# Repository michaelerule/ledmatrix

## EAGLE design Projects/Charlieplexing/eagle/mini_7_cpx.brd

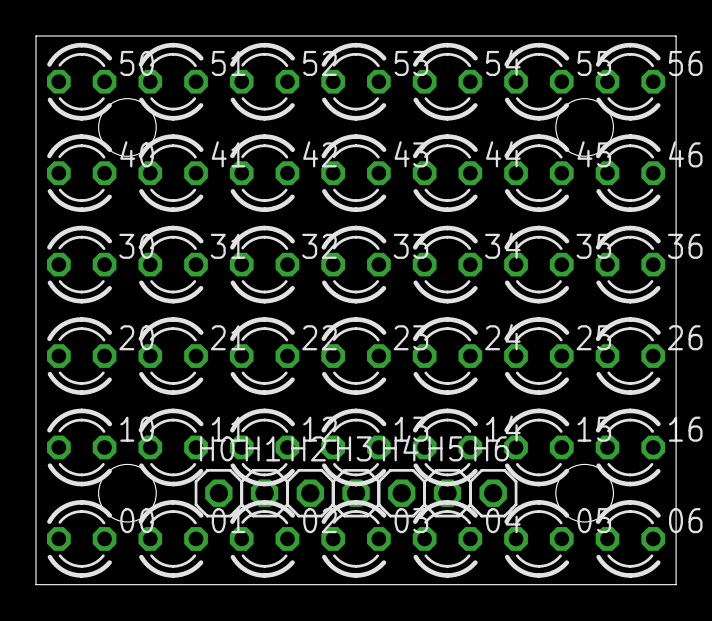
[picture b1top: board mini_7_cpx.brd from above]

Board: 2 copper layers, 35.6 x 30.5 mm, 49 parts (0 on the bottom side), 7 nets, no tracks yet.

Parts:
00, 01, 02, 03, 04, 05, 06, 10, 11, 12, 13, 14, 15, 16, 20, 21, 22, 23, 24, 25, 26, 30, 31, 32, 33, 34, 35, 36, 40, 41, 42, 43, 44, 45, 46, 50, 51, 52, 53, 54, 55, 56: LED3MM
H0, H1, H2, H3, H4, H5, H6: 1X01

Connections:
D: 00.A, 06.K, 11.A, 16.K, 22.A, 26.K, 33.A, 36.K, 44.A, 46.K, 55.A, 56.K, H6.1
S0: 00.K, 01.A, 02.A, 03.A, 04.A, 05.A, 06.A, 10.K, 20.K, 30.K, 40.K, 50.K, H0.1
S1: 01.K, 10.A, 11.K, 12.A, 13.A, 14.A, 15.A, 16.A, 21.K, 31.K, 41.K, 51.K, H1.1
S2: 02.K, 12.K, 20.A, 21.A, 22.K, 23.A, 24.A, 25.A, 26.A, 32.K, 42.K, 52.K, H2.1
S3: 03.K, 13.K, 23.K, 30.A, 31.A, 32.A, 33.K, 34.A, 35.A, 36.A, 43.K, 53.K, H3.1
S4: 04.K, 14.K, 24.K, 34.K, 40.A, 41.A, 42.A, 43.A, 44.K, 45.A, 46.A, 54.K, H4.1
S5: 05.K, 15.K, 25.K, 35.K, 45.K, 50.A, 51.A, 52.A, 53.A, 54.A, 55.K, 56.A, H5.1

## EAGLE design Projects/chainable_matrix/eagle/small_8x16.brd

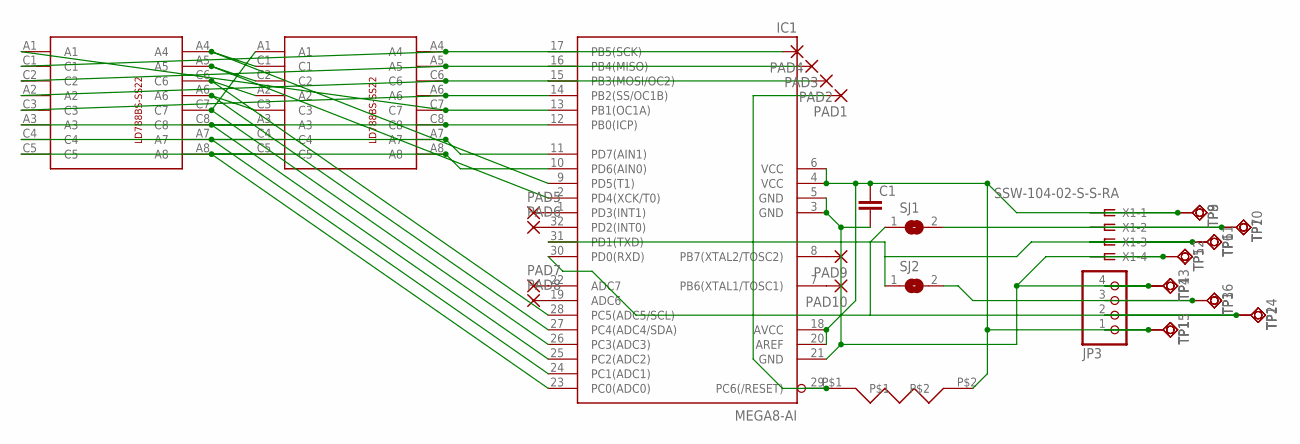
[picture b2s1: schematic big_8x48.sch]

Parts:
C1: CAPPTH; CAP-PTH-SMALL
IC1: MEGA8-AI; TQFP32-08
JP3: PINHD-1X4/90; 1X04/90
PAD1, PAD2, PAD3, PAD4, PAD5, PAD6, PAD7, PAD8, PAD9, PAD10: 1,6/0,8
SJ1, SJ2: SJ
TP1, TP2, TP3, TP4, TP5, TP6, TP7, TP8, TP9, TP10, TP11, TP12, TP13, TP14, TP15, TP16: TPSQTP20SQ; TP20SQ
U$1, U$2: LD-1088BS
U$3: R-6
X1: SSW-104-02-S-S-RA

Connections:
unnamed: IC1.24 (PC1(ADC1)), U$1.A7, U$2.C4
unnamed: IC1.25 (PC2(ADC2)), U$1.C8, U$2.A3
unnamed: IC1.26 (PC3(ADC3)), U$1.C7, U$2.A1
unnamed: IC1.27 (PC4(ADC4/SDA)), U$1.A6, U$2.C3
unnamed: IC1.28 (PC5(ADC5/SCL)), U$1.C6, U$2.A2
unnamed: IC1.2 (PD4(XCK/T0)), U$1.A5, U$2.C2
unnamed: IC1.9 (PD5(T1)), U$1.A4, U$2.C1
unnamed: IC1.15 (PB3(MOSI/OC2)), PAD2.1, U$1.A2, U$2.C6
unnamed: IC1.14 (PB2(SS/OC1B)), U$1.C3, U$2.A6
unnamed: IC1.13 (PB1(OC1A)), U$1.A1, U$2.C7
unnamed: IC1.12 (PB0(ICP)), U$1.A3, U$2.C8
unnamed: IC1.11 (PD7(AIN1)), U$1.C4, U$2.A7
unnamed: IC1.10 (PD6(AIN0)), U$1.C5, U$2.A8
unnamed: IC1.16 (PB4(MISO)), PAD3.1, U$1.C2, U$2.A5
unnamed: IC1.17 (PB5(SCK)), PAD4.1, U$1.C1, U$2.A4
unnamed: IC1.1 (PD3(INT1)), PAD5.1
unnamed: IC1.23 (PC0(ADC0)), U$1.A8, U$2.C5
unnamed: C1.2, IC1.3 (GND), IC1.5 (GND), IC1.21 (GND), JP3.4, TP4.TP, TP5.TP, TP12.TP, TP13.TP, X1.4
unnamed: C1.1, IC1.4 (VCC), IC1.6 (VCC), IC1.18 (AVCC), IC1.20 (AREF), JP3.1, TP1.TP, TP8.TP, TP9.TP, TP15.TP, U$3.P$2, X1.1
unnamed: IC1.32 (PD2(INT0)), PAD6.1
unnamed: SJ1.2, TP7.TP, TP10.TP, X1.2
unnamed: JP3.3, SJ2.2, TP3.TP, TP16.TP
unnamed: IC1.31 (PD1(TXD)), SJ2.1, TP6.TP, TP11.TP, X1.3
unnamed: IC1.30 (PD0(RXD)), JP3.2, SJ1.1, TP2.TP, TP14.TP
unnamed: IC1.29 (PC6(/RESET)), PAD1.1, U$3.P$1
unnamed: IC1.22 (ADC7), PAD7.1
unnamed: IC1.19 (ADC6), PAD8.1
unnamed: IC1.8 (PB7(XTAL2/TOSC2)), PAD9.1
unnamed: IC1.7 (PB6(XTAL1/TOSC1)), PAD10.1

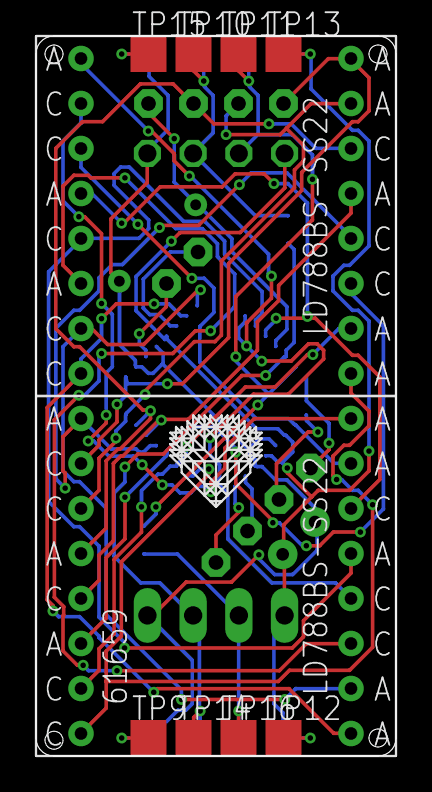
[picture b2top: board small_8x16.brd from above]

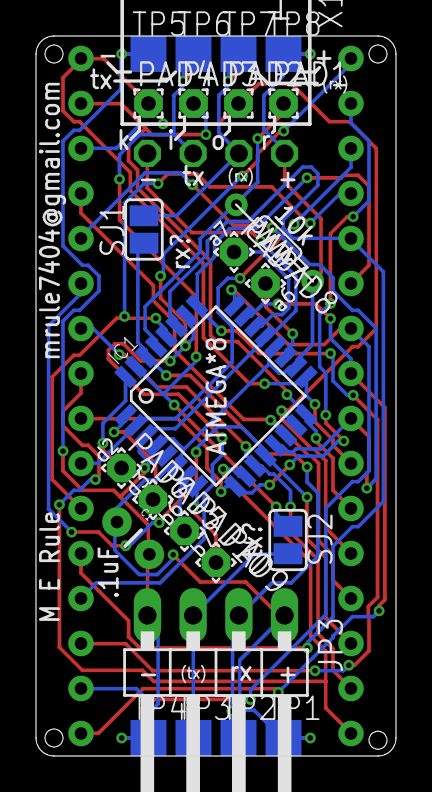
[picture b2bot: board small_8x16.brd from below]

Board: 2 copper layers, 20.0 x 40.0 mm, 36 parts (25 on the bottom side), 29 nets.

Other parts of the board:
U$4: LOGO

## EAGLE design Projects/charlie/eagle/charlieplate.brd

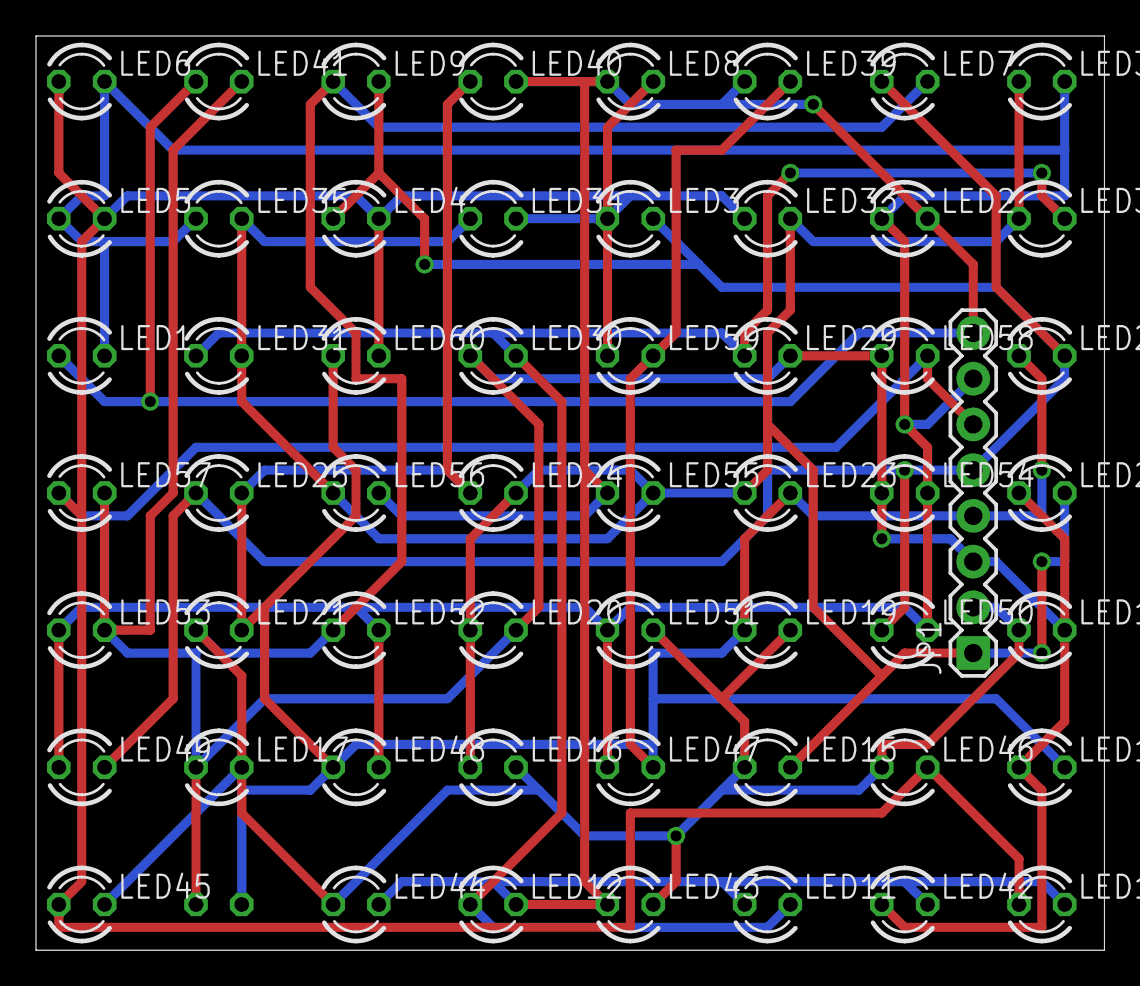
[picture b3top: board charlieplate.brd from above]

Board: 2 copper layers, 59.4 x 50.8 mm, 57 parts (1 on the bottom side), 9 nets.

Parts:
JP1: 1X08
LED1, LED2, LED3, LED4, LED5, LED6, LED7, LED8, LED9, LED10, LED11, LED12, LED13, LED14, LED15, LED16, LED17, LED18, LED19, LED20, LED21, LED22, LED23, LED24, LED25, LED26, LED29, LED30, LED31, LED32, LED33, LED34, LED35, LED36, LED39, LED40, LED41, LED42, LED43, LED44, LED45, LED46, LED47, LED48, LED49, LED50, LED51, LED52, LED53, LED54, LED55, LED56, LED57, LED58, LED59, LED60: LED3MM

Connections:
unnamed: JP1.8, LED1.A, LED2.K, LED8.A, LED10.K, LED11.A, LED12.K, LED39.A, LED40.K, LED41.A, LED42.K, LED43.A, LED44.K, LED55.A, LED56.K
unnamed: LED11.K, LED12.A, LED29.A, LED30.K, LED31.A, LED32.K
unnamed: JP1.1, LED15.K, LED16.A, LED20.A, LED22.K, LED23.A, LED24.K, LED31.K, LED32.A, LED33.K, LED34.A, LED35.K, LED36.A, LED55.K, LED56.A
unnamed: JP1.3, LED13.K, LED14.A, LED17.A, LED18.K, LED20.K, LED22.A, LED29.K, LED30.A, LED41.K, LED42.A, LED53.K, LED54.A, LED57.K, LED58.A
unnamed: JP1.6, LED3.A, LED4.K, LED5.K, LED6.A, LED8.K, LED10.A, LED33.A, LED34.K, LED45.A, LED46.K, LED57.A, LED58.K, LED59.A, LED60.K
unnamed: JP1.4, LED13.A, LED14.K, LED19.A, LED21.K, LED23.K, LED24.A, LED25.K, LED26.A, LED39.K, LED40.A, LED47.K, LED48.A, LED59.K, LED60.A
unnamed: JP1.5, LED3.K, LED4.A, LED7.A, LED9.K, LED25.A, LED26.K, LED49.K, LED50.A
unnamed: JP1.7, LED1.K, LED2.A, LED5.A, LED6.K, LED35.A, LED36.K, LED47.A, LED48.K, LED49.A, LED50.K, LED51.A, LED52.K, LED53.A, LED54.K
unnamed: JP1.2, LED7.K, LED9.A, LED15.A, LED16.K, LED17.K, LED18.A, LED19.K, LED21.A, LED43.K, LED44.A, LED45.K, LED46.A, LED51.K, LED52.A

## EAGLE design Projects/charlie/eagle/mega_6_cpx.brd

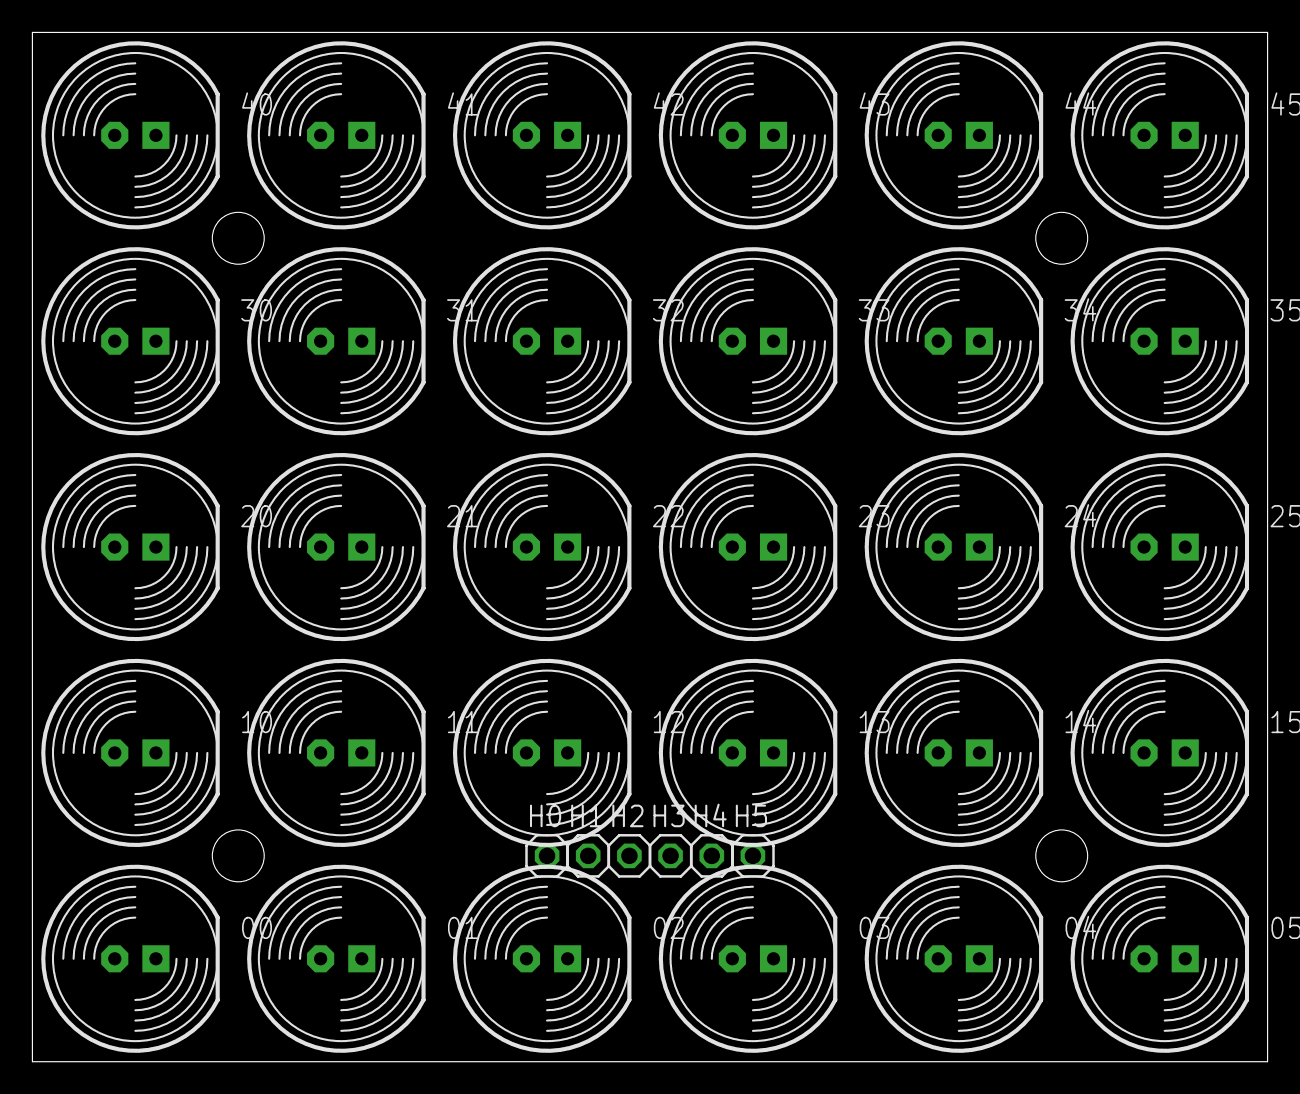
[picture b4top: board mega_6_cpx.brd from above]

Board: 2 copper layers, 76.2 x 63.5 mm, 36 parts (0 on the bottom side), 6 nets, no tracks yet.

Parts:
00, 01, 02, 03, 04, 05, 10, 11, 12, 13, 14, 15, 20, 21, 22, 23, 24, 25, 30, 31, 32, 33, 34, 35, 40, 41, 42, 43, 44, 45: LED10MM
H0, H1, H2, H3, H4, H5: 1X01

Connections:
D: 00.A, 05.K, 11.A, 15.K, 22.A, 25.K, 33.A, 35.K, 44.A, 45.K, H5.1
S0: 00.K, 01.A, 02.A, 03.A, 04.A, 05.A, 10.K, 20.K, 30.K, 40.K, H0.1
S1: 01.K, 10.A, 11.K, 12.A, 13.A, 14.A, 15.A, 21.K, 31.K, 41.K, H1.1
S2: 02.K, 12.K, 20.A, 21.A, 22.K, 23.A, 24.A, 25.A, 32.K, 42.K, H2.1
S3: 03.K, 13.K, 23.K, 30.A, 31.A, 32.A, 33.K, 34.A, 35.A, 43.K, H3.1
S4: 04.K, 14.K, 24.K, 34.K, 40.A, 41.A, 42.A, 43.A, 44.K, 45.A, H4.1

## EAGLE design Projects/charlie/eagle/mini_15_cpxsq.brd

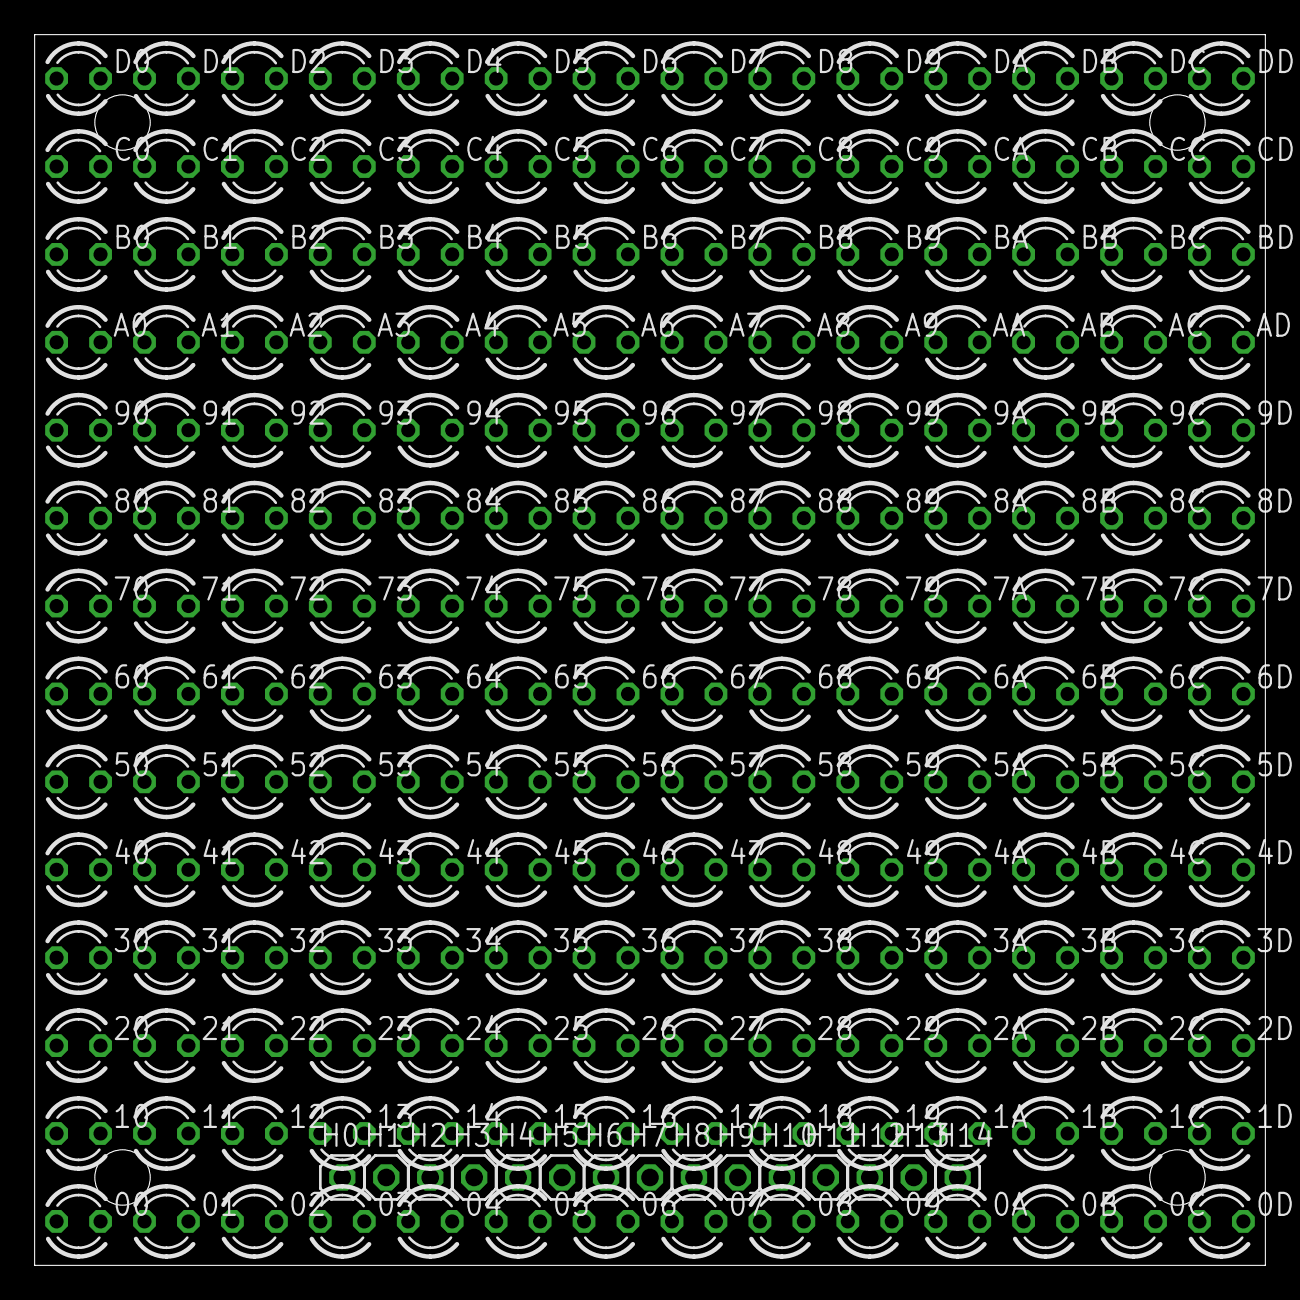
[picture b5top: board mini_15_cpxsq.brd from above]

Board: 2 copper layers, 71.1 x 71.1 mm, 211 parts (0 on the bottom side), 15 nets, no tracks yet.

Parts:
00, 0A, 0B, 0C, 0D, 01, 1A, 1B, 1C, 1D, 02, 2A, 2B, 2C, 2D, 03, 3A, 3B, 3C, 3D, 04, 4A, 4B, 4C, 4D, 05, 5A, 5B, 5C, 5D, 06, 6A, 6B, 6C, 6D, 07, 7A, 7B, 7C, 7D, 08, 8A, 8B, 8C, 8D, 09, 9A, 9B, 9C, 9D, 10, 11, 12, 13, 14, 15, 16, 17, 18, 19, 20, 21, 22, 23, 24, 25, 26, 27, 28, 29, 30, 31, 32, 33, 34, 35, 36, 37, 38, 39, 40, 41, 42, 43, 44, 45, 46, 47, 48, 49, 50, 51, 52, 53, 54, 55, 56, 57, 58, 59, 60, 61, 62, 63, 64, 65, 66, 67, 68, 69, 70, 71, 72, 73, 74, 75, 76, 77, 78, 79, 80, 81, 82, 83, 84, 85, 86, 87, 88, 89, 90, 91, 92, 93, 94, 95, 96, 97, 98, 99: LED3MM
A0, A1, A2, A3, A4, A5, A6, A7, A8, A9: LED3MM
AA: LED3MM
AB: LED3MM
AC: LED3MM
AD: LED3MM
B0, B1, B2, B3, B4, B5, B6, B7, B8, B9: LED3MM
BA: LED3MM
BB: LED3MM
BC: LED3MM
BD: LED3MM
C0, C1, C2, C3, C4, C5, C6, C7, C8, C9: LED3MM
CA: LED3MM
CB: LED3MM
CC: LED3MM
CD: LED3MM
D0, D1, D2, D3, D4, D5, D6, D7, D8, D9: LED3MM
DA: LED3MM
DB: LED3MM
DC: LED3MM
DD: LED3MM
H0, H1, H2, H3, H4, H5, H6, H7, H8, H9, H10, H11, H12, H13, H14: 1X01

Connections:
D: 00.A, 11.A, 22.A, 33.A, 44.A, 55.A, 66.A, 77.A, 88.A, 99.A, AA.A, BB.A, CC.A, DD.A, H14.1
S0: 00.K, 0A.A, 0B.A, 0C.A, 0D.A, 01.A, 02.A, 03.A, 04.A, 05.A, 06.A, 07.A, 08.A, 09.A, 10.K, 20.K, 30.K, 40.K, 50.K, 60.K, 70.K, 80.K, 90.K, A0.K, B0.K, C0.K, D0.K, H0.1
S1: 01.K, 1A.A, 1B.A, 1C.A, 1D.A, 10.A, 11.K, 12.A, 13.A, 14.A, 15.A, 16.A, 17.A, 18.A, 19.A, 21.K, 31.K, 41.K, 51.K, 61.K, 71.K, 81.K, 91.K, A1.K, B1.K, C1.K, D1.K, H1.1
S2: 02.K, 2A.A, 2B.A, 2C.A, 2D.A, 12.K, 20.A, 21.A, 22.K, 23.A, 24.A, 25.A, 26.A, 27.A, 28.A, 29.A, 32.K, 42.K, 52.K, 62.K, 72.K, 82.K, 92.K, A2.K, B2.K, C2.K, D2.K, H2.1
S3: 03.K, 3A.A, 3B.A, 3C.A, 3D.A, 13.K, 23.K, 30.A, 31.A, 32.A, 33.K, 34.A, 35.A, 36.A, 37.A, 38.A, 39.A, 43.K, 53.K, 63.K, 73.K, 83.K, 93.K, A3.K, B3.K, C3.K, D3.K, H3.1
S4: 04.K, 4A.A, 4B.A, 4C.A, 4D.A, 14.K, 24.K, 34.K, 40.A, 41.A, 42.A, 43.A, 44.K, 45.A, 46.A, 47.A, 48.A, 49.A, 54.K, 64.K, 74.K, 84.K, 94.K, A4.K, B4.K, C4.K, D4.K, H4.1
S5: 05.K, 5A.A, 5B.A, 5C.A, 5D.A, 15.K, 25.K, 35.K, 45.K, 50.A, 51.A, 52.A, 53.A, 54.A, 55.K, 56.A, 57.A, 58.A, 59.A, 65.K, 75.K, 85.K, 95.K, A5.K, B5.K, C5.K, D5.K, H5.1
S6: 06.K, 6A.A, 6B.A, 6C.A, 6D.A, 16.K, 26.K, 36.K, 46.K, 56.K, 60.A, 61.A, 62.A, 63.A, 64.A, 65.A, 66.K, 67.A, 68.A, 69.A, 76.K, 86.K, 96.K, A6.K, B6.K, C6.K, D6.K, H6.1
S7: 07.K, 7A.A, 7B.A, 7C.A, 7D.A, 17.K, 27.K, 37.K, 47.K, 57.K, 67.K, 70.A, 71.A, 72.A, 73.A, 74.A, 75.A, 76.A, 77.K, 78.A, 79.A, 87.K, 97.K, A7.K, B7.K, C7.K, D7.K, H7.1
S8: 08.K, 8A.A, 8B.A, 8C.A, 8D.A, 18.K, 28.K, 38.K, 48.K, 58.K, 68.K, 78.K, 80.A, 81.A, 82.A, 83.A, 84.A, 85.A, 86.A, 87.A, 88.K, 89.A, 98.K, A8.K, B8.K, C8.K, D8.K, H8.1
S9: 09.K, 9A.A, 9B.A, 9C.A, 9D.A, 19.K, 29.K, 39.K, 49.K, 59.K, 69.K, 79.K, 89.K, 90.A, 91.A, 92.A, 93.A, 94.A, 95.A, 96.A, 97.A, 98.A, 99.K, A9.K, B9.K, C9.K, D9.K, H9.1
S10: 0A.K, 1A.K, 2A.K, 3A.K, 4A.K, 5A.K, 6A.K, 7A.K, 8A.K, 9A.K, A0.A, A1.A, A2.A, A3.A, A4.A, A5.A, A6.A, A7.A, A8.A, A9.A, AA.K, AB.A, AC.A, AD.A, BA.K, CA.K, DA.K, H10.1
S11: 0B.K, 1B.K, 2B.K, 3B.K, 4B.K, 5B.K, 6B.K, 7B.K, 8B.K, 9B.K, AB.K, B0.A, B1.A, B2.A, B3.A, B4.A, B5.A, B6.A, B7.A, B8.A, B9.A, BA.A, BB.K, BC.A, BD.A, CB.K, DB.K, H11.1
S12: 0C.K, 1C.K, 2C.K, 3C.K, 4C.K, 5C.K, 6C.K, 7C.K, 8C.K, 9C.K, AC.K, BC.K, C0.A, C1.A, C2.A, C3.A, C4.A, C5.A, C6.A, C7.A, C8.A, C9.A, CA.A, CB.A, CC.K, CD.A, DC.K, H12.1
S13: 0D.K, 1D.K, 2D.K, 3D.K, 4D.K, 5D.K, 6D.K, 7D.K, 8D.K, 9D.K, AD.K, BD.K, CD.K, D0.A, D1.A, D2.A, D3.A, D4.A, D5.A, D6.A, D7.A, D8.A, D9.A, DA.A, DB.A, DC.A, DD.K, H13.1

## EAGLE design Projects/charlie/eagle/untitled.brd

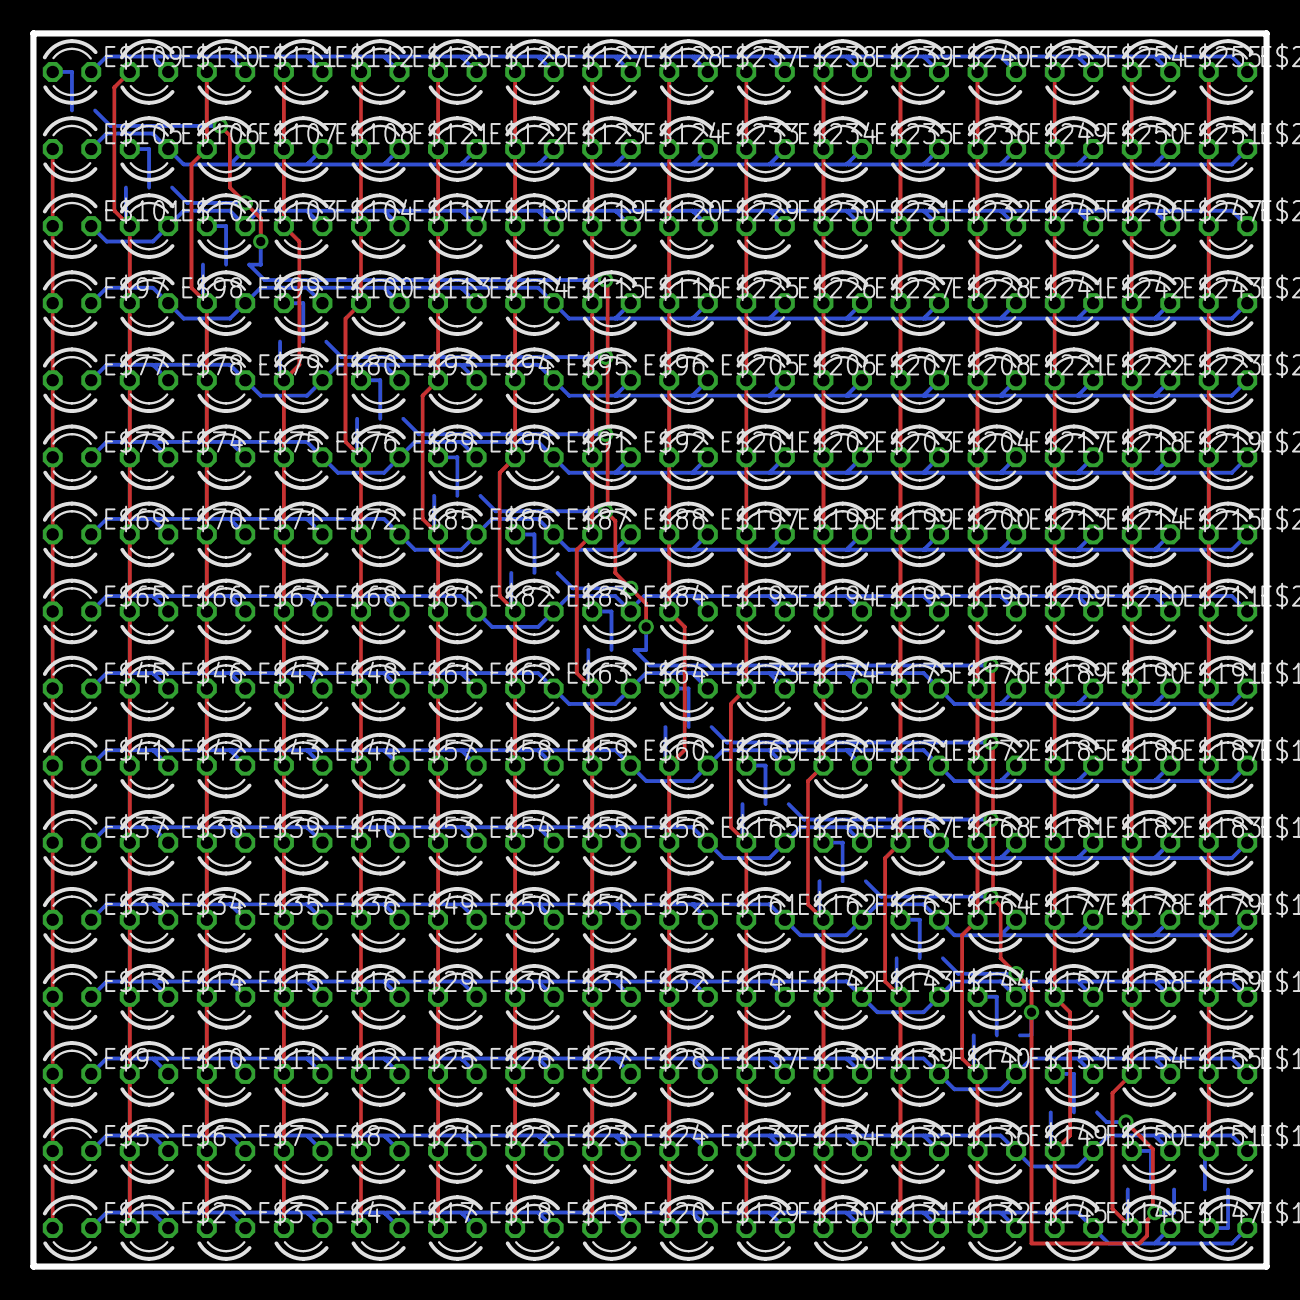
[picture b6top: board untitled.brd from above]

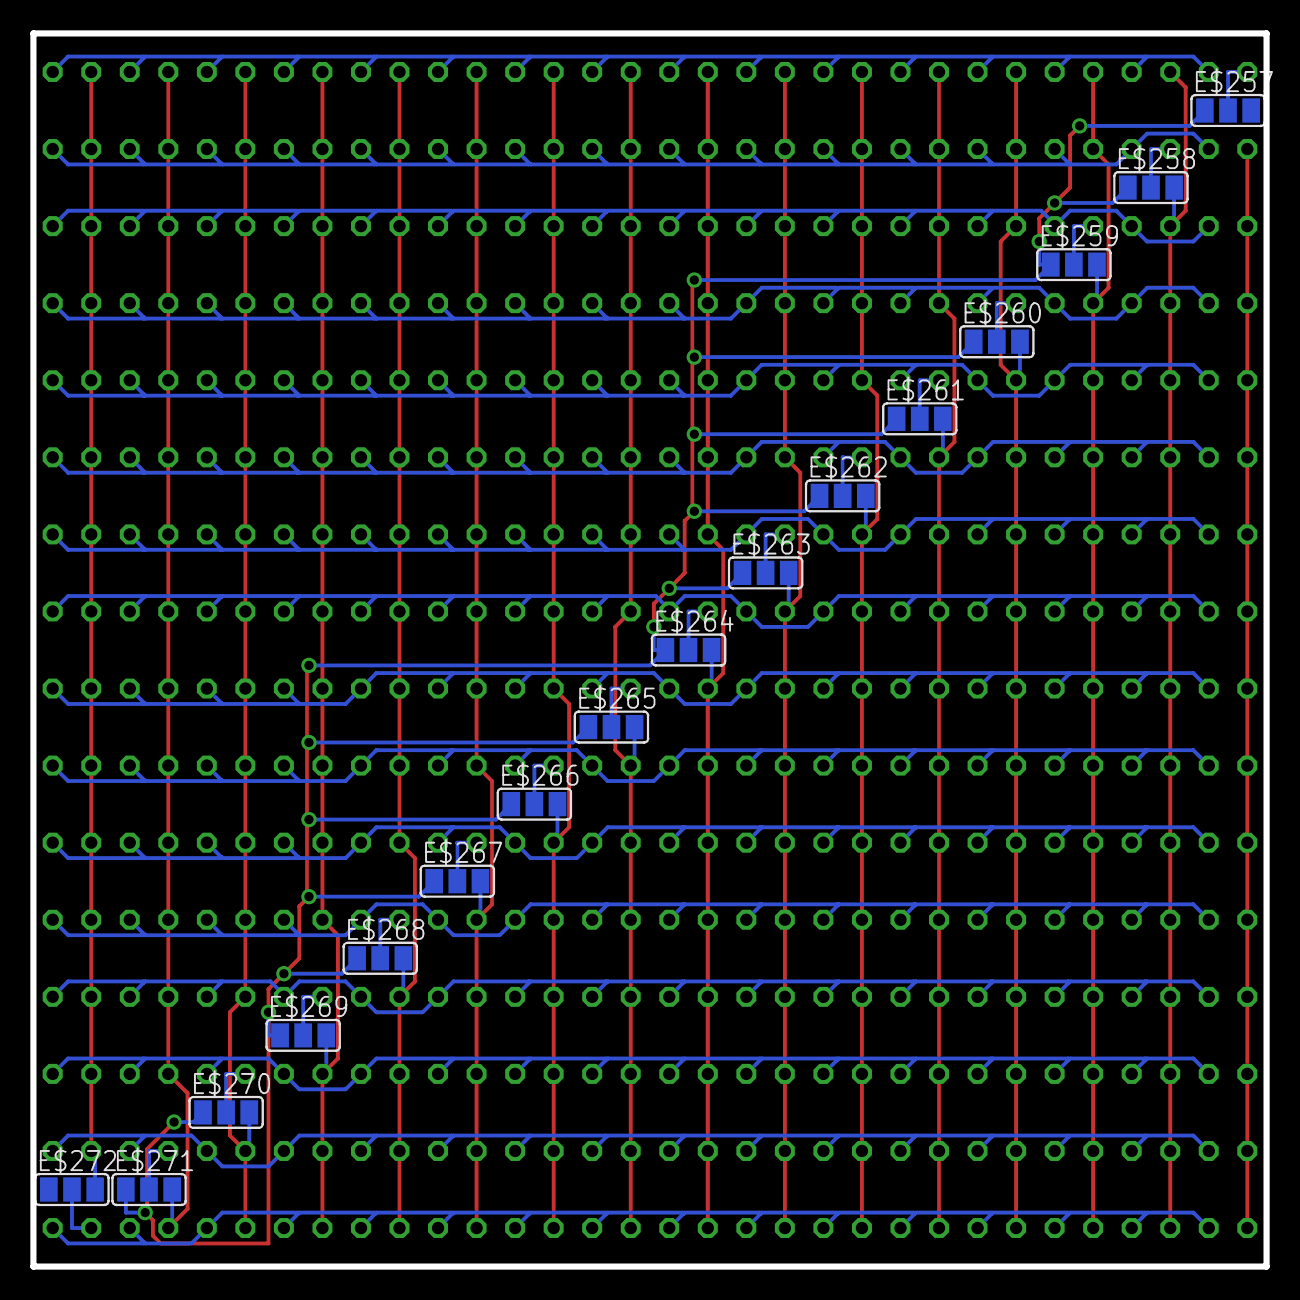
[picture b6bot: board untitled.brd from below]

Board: 2 copper layers, 81.3 x 81.3 mm, 272 parts (16 on the bottom side), 49 nets.

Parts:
E$1, E$2, E$3, E$4, E$5, E$6, E$7, E$8, E$9, E$10, E$11, E$12, E$13, E$14, E$15, E$16, E$17, E$18, E$19, E$20, E$21, E$22, E$23, E$24, E$25, E$26, E$27, E$28, E$29, E$30, E$31, E$32, E$33, E$34, E$35, E$36, E$37, E$38, E$39, E$40, E$41, E$42, E$43, E$44, E$45, E$46, E$47, E$48, E$49, E$50, E$51, E$52, E$53, E$54, E$55, E$56, E$57, E$58, E$59, E$60, E$61, E$62, E$63, E$64, E$65, E$66, E$67, E$68, E$69, E$70, E$71, E$72, E$73, E$74, E$75, E$76, E$77, E$78, E$79, E$80, E$81, E$82, E$83, E$84, E$85, E$86, E$87, E$88, E$89, E$90, E$91, E$92, E$93, E$94, E$95, E$96, E$97, E$98, E$99, E$100, E$101, E$102, E$103, E$104, E$105, E$106, E$107, E$108, E$109, E$110, E$111, E$112, E$113, E$114, E$115, E$116, E$117, E$118, E$119, E$120, E$121, E$122, E$123, E$124, E$125, E$126, E$127, E$128, E$129, E$130, E$131, E$132, E$133, E$134, E$135, E$136, E$137, E$138, E$139, E$140, E$141, E$142, E$143, E$144, E$145, E$146, E$147, E$148, E$149, E$150, E$151, E$152, E$153, E$154, E$155, E$156, E$157, E$158, E$159, E$160, E$161, E$162, E$163, E$164, E$165, E$166, E$167, E$168, E$169, E$170, E$171, E$172, E$173, E$174, E$175, E$176, E$177, E$178, E$179, E$180, E$181, E$182, E$183, E$184, E$185, E$186, E$187, E$188, E$189, E$190, E$191, E$192, E$193, E$194, E$195, E$196, E$197, E$198, E$199, E$200, E$201, E$202, E$203, E$204, E$205, E$206, E$207, E$208, E$209, E$210, E$211, E$212, E$213, E$214, E$215, E$216, E$217, E$218, E$219, E$220, E$221, E$222, E$223, E$224, E$225, E$226, E$227, E$228, E$229, E$230, E$231, E$232, E$233, E$234, E$235, E$236, E$237, E$238, E$239, E$240, E$241, E$242, E$243, E$244, E$245, E$246, E$247, E$248, E$249, E$250, E$251, E$252, E$253, E$254, E$255, E$256: LED3MM
E$257, E$258, E$259, E$260, E$261, E$262, E$263, E$264, E$265, E$266, E$267, E$268, E$269, E$270, E$271, E$272: SJ_2

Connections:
S$1: E$1.A, E$5.A, E$9.A, E$13.A, E$33.A, E$37.A, E$41.A, E$45.A, E$65.A, E$69.A, E$73.A, E$77.A, E$97.A, E$101.A, E$105.A, E$257.3
S$2: E$2.A, E$6.A, E$10.A, E$14.A, E$34.A, E$38.A, E$42.A, E$46.A, E$66.A, E$70.A, E$74.A, E$78.A, E$98.A, E$102.A, E$110.A, E$258.3
S$3: E$3.A, E$7.A, E$11.A, E$15.A, E$35.A, E$39.A, E$43.A, E$47.A, E$67.A, E$71.A, E$75.A, E$79.A, E$99.A, E$107.A, E$111.A, E$259.3
S$4: E$4.A, E$8.A, E$12.A, E$16.A, E$36.A, E$40.A, E$44.A, E$48.A, E$68.A, E$72.A, E$76.A, E$80.A, E$104.A, E$108.A, E$112.A, E$260.3
S$5: E$17.A, E$21.A, E$25.A, E$29.A, E$49.A, E$53.A, E$57.A, E$61.A, E$81.A, E$85.A, E$89.A, E$113.A, E$117.A, E$121.A, E$125.A, E$261.3
S$6: E$18.A, E$22.A, E$26.A, E$30.A, E$50.A, E$54.A, E$58.A, E$62.A, E$82.A, E$86.A, E$94.A, E$114.A, E$118.A, E$122.A, E$126.A, E$262.3
S$7: E$19.A, E$23.A, E$27.A, E$31.A, E$51.A, E$55.A, E$59.A, E$63.A, E$83.A, E$91.A, E$95.A, E$115.A, E$119.A, E$123.A, E$127.A, E$263.3
S$8: E$109.A, E$257.2
S$9: E$152.A, E$156.A, E$160.A, E$180.A, E$184.A, E$188.A, E$192.A, E$212.A, E$216.A, E$220.A, E$224.A, E$244.A, E$248.A, E$252.A, E$256.A, E$272.3
S$10: E$147.A, E$155.A, E$159.A, E$179.A, E$183.A, E$187.A, E$191.A, E$211.A, E$215.A, E$219.A, E$223.A, E$243.A, E$247.A, E$251.A, E$255.A, E$271.3
S$11: E$146.A, E$150.A, E$158.A, E$178.A, E$182.A, E$186.A, E$190.A, E$210.A, E$214.A, E$218.A, E$222.A, E$242.A, E$246.A, E$250.A, E$254.A, E$270.3
S$12: E$145.A, E$149.A, E$153.A, E$177.A, E$181.A, E$185.A, E$189.A, E$209.A, E$213.A, E$217.A, E$221.A, E$241.A, E$245.A, E$249.A, E$253.A, E$269.3
S$13: E$132.A, E$136.A, E$140.A, E$144.A, E$168.A, E$172.A, E$176.A, E$196.A, E$200.A, E$204.A, E$208.A, E$228.A, E$232.A, E$236.A, E$240.A, E$268.3
S$14: E$131.A, E$135.A, E$139.A, E$143.A, E$163.A, E$171.A, E$175.A, E$195.A, E$199.A, E$203.A, E$207.A, E$227.A, E$231.A, E$235.A, E$239.A, E$267.3
S$15: E$130.A, E$134.A, E$138.A, E$142.A, E$162.A, E$166.A, E$174.A, E$194.A, E$198.A, E$202.A, E$206.A, E$226.A, E$230.A, E$234.A, E$238.A, E$266.3
S$16: E$129.A, E$133.A, E$137.A, E$141.A, E$161.A, E$165.A, E$169.A, E$193.A, E$197.A, E$201.A, E$205.A, E$225.A, E$229.A, E$233.A, E$237.A, E$265.3
S$17: E$20.A, E$24.A, E$28.A, E$32.A, E$52.A, E$56.A, E$60.A, E$64.A, E$88.A, E$92.A, E$96.A, E$116.A, E$120.A, E$124.A, E$128.A, E$264.3
S$18: E$1.K, E$2.K, E$3.K, E$4.K, E$17.K, E$18.K, E$19.K, E$20.K, E$129.K, E$130.K, E$131.K, E$132.K, E$145.K, E$146.K, E$147.K, E$148.K
S$19: E$5.K, E$6.K, E$7.K, E$8.K, E$21.K, E$22.K, E$23.K, E$24.K, E$133.K, E$134.K, E$135.K, E$136.K, E$149.K, E$150.K, E$151.K, E$152.K
S$20: E$9.K, E$10.K, E$11.K, E$12.K, E$25.K, E$26.K, E$27.K, E$28.K, E$137.K, E$138.K, E$139.K, E$140.K, E$153.K, E$154.K, E$155.K, E$156.K
S$21: E$13.K, E$14.K, E$15.K, E$16.K, E$29.K, E$30.K, E$31.K, E$32.K, E$141.K, E$142.K, E$143.K, E$144.K, E$157.K, E$158.K, E$159.K, E$160.K
S$22: E$33.K, E$34.K, E$35.K, E$36.K, E$49.K, E$50.K, E$51.K, E$52.K, E$161.K, E$162.K, E$163.K, E$164.K, E$177.K, E$178.K, E$179.K, E$180.K
S$23: E$37.K, E$38.K, E$39.K, E$40.K, E$53.K, E$54.K, E$55.K, E$56.K, E$165.K, E$166.K, E$167.K, E$168.K, E$181.K, E$182.K, E$183.K, E$184.K
S$24: E$41.K, E$42.K, E$43.K, E$44.K, E$57.K, E$58.K, E$59.K, E$60.K, E$169.K, E$170.K, E$171.K, E$172.K, E$185.K, E$186.K, E$187.K, E$188.K
S$25: E$45.K, E$46.K, E$47.K, E$48.K, E$61.K, E$62.K, E$63.K, E$64.K, E$173.K, E$174.K, E$175.K, E$176.K, E$189.K, E$190.K, E$191.K, E$192.K
S$26: E$65.K, E$66.K, E$67.K, E$68.K, E$81.K, E$82.K, E$83.K, E$84.K, E$193.K, E$194.K, E$195.K, E$196.K, E$209.K, E$210.K, E$211.K, E$212.K
S$27: E$69.K, E$70.K, E$71.K, E$72.K, E$85.K, E$86.K, E$87.K, E$88.K, E$197.K, E$198.K, E$199.K, E$200.K, E$213.K, E$214.K, E$215.K, E$216.K
S$28: E$73.K, E$74.K, E$75.K, E$76.K, E$89.K, E$90.K, E$91.K, E$92.K, E$201.K, E$202.K, E$203.K, E$204.K, E$217.K, E$218.K, E$219.K, E$220.K
S$29: E$77.K, E$78.K, E$79.K, E$80.K, E$93.K, E$94.K, E$95.K, E$96.K, E$205.K, E$206.K, E$207.K, E$208.K, E$221.K, E$222.K, E$223.K, E$224.K
S$30: E$97.K, E$98.K, E$99.K, E$100.K, E$113.K, E$114.K, E$115.K, E$116.K, E$225.K, E$226.K, E$227.K, E$228.K, E$241.K, E$242.K, E$243.K, E$244.K
S$31: E$101.K, E$102.K, E$103.K, E$104.K, E$117.K, E$118.K, E$119.K, E$120.K, E$229.K, E$230.K, E$231.K, E$232.K, E$245.K, E$246.K, E$247.K, E$248.K
S$32: E$105.K, E$106.K, E$107.K, E$108.K, E$121.K, E$122.K, E$123.K, E$124.K, E$233.K, E$234.K, E$235.K, E$236.K, E$249.K, E$250.K, E$251.K, E$252.K
S$33: E$109.K, E$110.K, E$111.K, E$112.K, E$125.K, E$126.K, E$127.K, E$128.K, E$237.K, E$238.K, E$239.K, E$240.K, E$253.K, E$254.K, E$255.K, E$256.K
S$34: E$106.A, E$258.2
S$35: E$103.A, E$259.2
S$36: E$100.A, E$260.2
S$37: E$93.A, E$261.2
S$38: E$90.A, E$262.2
S$39: E$148.A, E$272.2
S$40: E$87.A, E$263.2
S$41: E$84.A, E$264.2
S$42: E$173.A, E$265.2
S$43: E$170.A, E$266.2
S$44: E$167.A, E$267.2
S$45: E$164.A, E$268.2
S$46: E$157.A, E$269.2
S$47: E$154.A, E$270.2
S$48: E$151.A, E$271.2
S$49: E$257.1, E$258.1, E$259.1, E$260.1, E$261.1, E$262.1, E$263.1, E$264.1, E$265.1, E$266.1, E$267.1, E$268.1, E$269.1, E$270.1, E$271.1, E$272.1

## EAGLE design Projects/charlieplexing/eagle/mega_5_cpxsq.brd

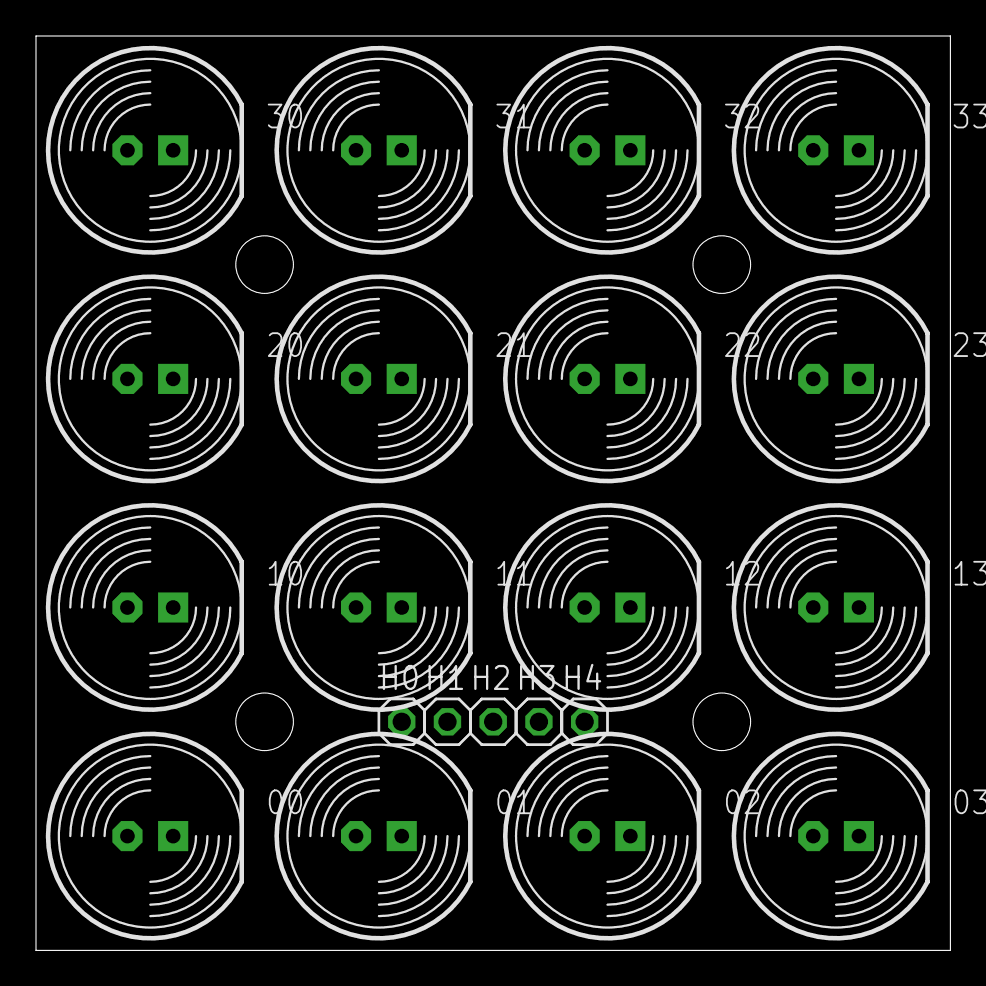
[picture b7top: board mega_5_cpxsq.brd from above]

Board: 2 copper layers, 50.8 x 50.8 mm, 21 parts (0 on the bottom side), 5 nets, no tracks yet.

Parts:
00, 01, 02, 03, 10, 11, 12, 13, 20, 21, 22, 23, 30, 31, 32, 33: LED10MM
H0, H1, H2, H3, H4: 1X01

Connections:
D: 00.A, 11.A, 22.A, 33.A, H4.1
S0: 00.K, 01.A, 02.A, 03.A, 10.K, 20.K, 30.K, H0.1
S1: 01.K, 10.A, 11.K, 12.A, 13.A, 21.K, 31.K, H1.1
S2: 02.K, 12.K, 20.A, 21.A, 22.K, 23.A, 32.K, H2.1
S3: 03.K, 13.K, 23.K, 30.A, 31.A, 32.A, 33.K, H3.1

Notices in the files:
parts and their libraries:
SparkFun: Licensing: CC v3.0 Share-Alike You are welcome to use this library for commercial purposes.
